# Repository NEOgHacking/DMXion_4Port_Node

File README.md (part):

# DMXion_4Port_Node
DMXion_4Port_Node is a DMX network node based on the official grandMA3 onPC 4Port Node 4k. My version also has 4DMX outputs with RDM support, a EtherCON connector for sturdy Ethernet connections and a display with a rotating knob for configuration. It also uses the Neutrik halo connectors with adressable rgb leds to show the status of the connection. But it also has some differences. First it unfortunately doesn't unlock any parameters in the GrandMA onPC software, but its 20x cheaper. About $100 instead of $2000.

# Features
This specific DMX node has some really usefull features.
1. 4DMX outputs with RDM support.
2. Neutrik EtherCON connector for a sturdy and lasting connection. Also support for ARTNET and sACN
3. Color display with a rotary encoder for configuration straigt from the unit itself.
4. UPS (uniteruptable power supply) For when the power cuts out but you still need it or just for battery operation.
5. Wifi card slot for wireless operation with the battery.
6. Powered by a rp2350 for its PIO modules so DMX is correctly implemented and not via a hacked uart or bitbanging a pin.
7. PoE (Power over Ethernet) For easy setup and as little wires as possible.
8. USB-C port for power and data to program the rp2350 or configure it.
9. Cheap PCB. The PCB is 100x72mm 4 layer so its cost is low only $7.

# Motivation
I started on making this DMX network node for a few reasons. First i was using a raspberry pi with a usb DMX dongle, this worked but was hard to set up and only got me 1 DMX universe without RDM. It also wasn't the cheapest setup. I wanted it to be cheaper and have more functionallity. Second I once had the opurtunity to use a grandMA3 onPC 4Port Node 4k at school once and realized how usefull it would be. Then my dumb brain said the same sentence it always says: "I can build that myself for cheaper right?" Next thing you know you are 100 hours deep into the project.

# Design
The design process was a heck of a ride, at first i started with the simple DMX part but then got to the ethernet. I really wanted PoE so started with the ride. It was a heck of a long ride, i think it took up 1/3 of the projects time its really complex. Also the most complex schematic from the whole project. The rest went pretty smooth. I had recently done another big project my 3D Printer mainboard and learned allot from that! So the rest was pretty straight forward, always some small chip changes here and there but apart from that it went well. The case design also went quick didn't have to high of standards for that but still wanted it to look good. After a whole day that was done. 
I used KiCad for PCB design, Onshape for 3D design and VScode for Firmware.

# Use
To use this product first get the firmware uploaded via the arduino IDE or PlatformIO Then just plug it into a ethernet setup and plug in your DMX devices. Thats it! Its that simple! For config use the display with the rotating knob to select universes, ethernet settings, ext.

# Schematic
This is a very long schematic. You can find the whole schematics in .PDF format in the individual PCB design folders. But here are some important ones.
First the main schematic of the main PCB.

Then the schematic of the display module.

And finally the esp wifi module.

# PCB's
So this project has 3 PCB's, first the main PCB that does all the hard work, then a display PCB with a rotary encoder and support components for a bare LCD and finally a custom made WIFI module PCB based on the esp.

(there is a glitch in this game, every project i do i get exactly 3 PCB's)

# Case
For this project there needed to be a case to protect the PCB from the outside world. I did this in onshape and am happy with the end result.

Here is the Onshape link:
https://cad.onshape.com/documents/7a1aa90c6a7c74ef8699231e/w/3ea57ea1703701009a206be9/e/21fe65d6bda3912845cd8de3?renderMode=0&uiState=69a73631645b04a633250657
<details>
  <summary>BOM</summary>
  
# BOM
| Id | Designator | Footprint | Quantity | Designation | Supplier and ref | Column1 | Needed quantity | - | LCSC | MOUSER | Already in another pcb | Enough? | Mrf# | Mfr. | Order Qty. | Unit Price(USD) | Ext.Price(USD) | LCSC#/MOUSER | Package | Min | Mult | SPQ | Availability | Stock Status | Customer Notes | Description | Matched status | Product Link |  |  |  |  |  |  |  |  |  |  |  |  |  |  |  |  |  |  |  |
| --- | --- | --- | --- | --- | --- | --- | --- | --- | --- | --- | --- | --- | --- | --- | --- | --- | --- | --- | --- | --- | --- | --- | --- | --- | --- | --- | --- | --- | --- | --- | --- | --- | --- | --- | --- | --- | --- | --- | --- | --- | --- | --- | --- | --- | --- | --- | --- |
| 17 | BT1 | JST_XH_B3B-XH-A_1x03_P2.50mm_Vertical | 1 | Battery_Cell |  |  | 2 |  | x |  |  |  | B3B-XH-A(LF)(SN) | JST | 10 | $0.05 | $0.50 | C144394 | Through Hole,P=2.5mm | 10 | 10 | 1000 | 61980 | In Stock |  | Connector Header 3 position 2.5mm Pitch 3A Through Hole -25?~+85? | Exact Matches | https://www.lcsc.com/product-detail/C144394.html |  |  |  |  |  |  |  |  |  |  |  |  |  |  |  |  |  |  |  |
| 6 | C12,C7,C5,C13,C11,C4,C6,C3,C9,C10,C8,C1 | C_0402_1005Metric | 12 | 100n |  |  | 24 |  | x |  |  |  | CL05B104KO5NNNC | Samsung Electro-Mechanics | 100 | $0.00 | $0.13 | C1525 | 402 | 100 | 100 | 10000 | 22016000 | In Stock |  | 100nF �10% 16V Ceramic Capacitor X7R 0402 | Exact Matches | https://www.lcsc.com/product-detail/C1525.html |  |  |  |  |  |  |  |  |  |  |  |  |  |  |  |  |  |  |  |
| 37 | C17,C19 | C_0402_1005Metric | 2 | 15p |  |  | 4 |  | x |  |  |  | CL05C150JB5NNNC | Samsung Electro-Mechanics | 100 | $0.00 | $0.37 | C86285 | 402 | 100 | 100 | 10000 | 454800 | In Stock |  | 15pF �5% 50V Ceramic Capacitor C0G 0402 | Exact Matches | https://www.lcsc.com/product-detail/C86285.html |  |  |  |  |  |  |  |  |  |  |  |  |  |  |  |  |  |  |  |
| 3 | C2,C15,C16,C14 | C_0402_1005Metric | 4 | 4u7 |  |  | 8 |  | x |  |  |  | CL05A475KP5NRNC | Samsung Electro-Mechanics | 50 | $0.01 | $0.31 | C368809 | 402 | 50 | 50 | 10000 | 5001000 | In Stock |  | 4.7uF �10% 10V Ceramic Capacitor X5R 0402 | Exact Matches | https://www.lcsc.com/product-detail/C368809.html |  |  |  |  |  |  |  |  |  |  |  |  |  |  |  |  |  |  |  |
| 9 | C20,C23,C57,C33,C21 | C_0603_1608Metric | 5 | 10n |  |  | 10 |  | x |  |  |  | CL10B103KC8NNNC | Samsung Electro-Mechanics | 100 | $0.01 | $0.62 | C84709 | 603 | 100 | 100 | 4000 | 18800 | In Stock |  | 10nF �10% 100V Ceramic Capacitor X7R 0603 | Exact Matches | https://www.lcsc.com/product-detail/C84709.html |  |  |  |  |  |  |  |  |  |  |  |  |  |  |  |  |  |  |  |
| 15 | C22,C36,C39,C41,C34,C38,C63,C37,C65,C47,C40,C35 | C_0603_1608Metric | 12 | 1n |  |  | 24 |  | x |  |  |  | CL10B102KC8NNNC | Samsung Electro-Mechanics | 50 | $0.01 | $0.25 | C153291 | 603 | 50 | 50 | 4000 | 107650 | In Stock |  | 1nF �10% 100V Ceramic Capacitor X7R 0603 | Exact Matches | https://www.lcsc.com/product-detail/C153291.html |  |  |  |  |  |  |  |  |  |  |  |  |  |  |  |  |  |  |  |
| 5 | C27,C76,C72,C70,C73,C64,C79,C60,C28,C74,C29,C88,C43,C78,C61,C71,C30,C66,C69,C68,C25,C42,C75,C67,C45,C31,C18,C26,C77 | C_0603_1608Metric | 29 | 100n |  |  | 58 |  | x |  |  |  | CL10B104KC8NNNC | Samsung Electro-Mechanics | 100 | $0.01 | $0.65 | C15725 | 603 | 50 | 50 | 4000 | 175750 | In Stock |  | 100nF �10% 100V Ceramic Capacitor X7R 0603 | Exact Matches | https://www.lcsc.com/product-detail/C15725.html |  |  |  |  |  |  |  |  |  |  |  |  |  |  |  |  |  |  |  |
| 63 | C32,C24 | CP_EIA-2012-12_Kemet-R | 2 | 10u |  |  | 4 |  | x |  |  |  | T491A106K006AT | KEMET | 5 | $0.18 | $0.91 | C122260 | CASE-A-3216-18(mm) | 5 | 5 | 2000 | 1980 | In Stock |  | 10uF �10% 6.3V Tantalum Capacitors 4?@100kHz CASE-A-3216-18(mm) | Exact Matches | https://www.lcsc.com/product-detail/C122260.html |  |  |  |  |  |  |  |  |  |  |  |  |  |  |  |  |  |  |  |
| 50 | C46,C44 | C_0603_1608Metric | 2 | 6.8n |  |  | 4 |  | x |  |  |  | CL10B682KB8NNNC | Samsung Electro-Mechanics | 100 | $0.01 | $0.68 | C84723 | 603 | 100 | 100 | 4000 | 5300 | In Stock |  | 6.8nF �10% 50V Ceramic Capacitor X7R 0603 | Exact Matches | https://www.lcsc.com/product-detail/C84723.html |  |  |  |  |  |  |  |  |  |  |  |  |  |  |  |  |  |  |  |
| 8 | C48,C49 | C_0603_1608Metric | 2 | 10p |  |  | 4 |  | x |  |  |  | CL10C100JB8NNNC | Samsung Electro-Mechanics | 100 | $0.01 | $0.50 | C1634 | 603 | 100 | 100 | 4000 | 1498600 | In Stock |  | 10pF �5% 50V Ceramic Capacitor C0G 0603 | Exact Matches | https://www.lcsc.com/product-detail/C1634.html |  |  |  |  |  |  |  |  |  |  |  |  |  |  |  |  |  |  |  |
| 41 | C52,C51,C50 | C_0805_2012Metric | 3 | 1u |  |  | 6 |  | x |  |  |  | C2012X7S2A105KT000N | TDK | 10 | $0.11 | $1.12 | C342785 | 805 | 5 | 5 | 2000 | 5645 | In Stock |  | 1uF �10% 100V Ceramic Capacitor X7S 0805 | Exact Matches | https://www.lcsc.com/product-detail/C342785.html |  |  |  |  |  |  |  |  |  |  |  |  |  |  |  |  |  |  |  |
| 57 | C53 | CP_Elec_6.3x5.8 | 1 | 10u |  |  | 2 |  | x |  |  |  | EEEFK1J100P | PANASONIC | 5 | $0.14 | $0.71 | C128459 | SMD,D6.3xL5.8mm | 5 | 5 | 1000 | 1420 | In Stock |  | 10uF �20% 63V Aluminum Electrolytic Capacitors 2000hrs@105? | Exact Matches | https://www.lcsc.com/product-detail/C128459.html |  |  |  |  |  |  |  |  |  |  |  |  |  |  |  |  |  |  |  |
| 69 | C54 | C_0603_1608Metric | 1 | 470p |  |  | 2 |  | x |  |  |  | CL10B471KB8NNNC | Samsung Electro-Mechanics | 100 | $0.01 | $0.56 | C22396 | 603 | 100 | 100 | 4000 | 189700 | In Stock |  | 470pF �10% 50V Ceramic Capacitor X7R 0603 | Exact Matches | https://www.lcsc.com/product-detail/C22396.html |  |  |  |  |  |  |  |  |  |  |  |  |  |  |  |  |  |  |  |
| 44 | C55 | CP_Elec_10x10.5 | 1 | 1000u |  |  | 2 |  | x |  |  |  | EEEFT1E102UP | PANASONIC | 2 | $0.78 | $1.55 | C401766 | SMD,D10xL10.2mm | 1 | 1 | 500 | 4041 | In Stock |  | 1000uF �20% 25V Aluminum Electrolytic Capacitors 2000hrs@105? | Exact Matches | https://www.lcsc.com/product-detail/C401766.html |  |  |  |  |  |  |  |  |  |  |  |  |  |  |  |  |  |  |  |
| 52 | C56 | C_1206_3216Metric | 1 | 100u |  |  | 2 |  | x |  |  |  | CL31A107MQHNNNE | Samsung Electro-Mechanics | 10 | $0.06 | $0.61 | C15008 | 1206 | 10 | 10 | 2000 | 6009890 | In Stock |  | 100uF �20% 6.3V Ceramic Capacitor X5R 1206 | Exact Matches | https://www.lcsc.com/product-detail/C15008.html |  |  |  |  |  |  |  |  |  |  |  |  |  |  |  |  |  |  |  |
| 14 | C58 | C_0603_1608Metric | 1 | 4u7 |  |  | 2 |  | x |  |  |  | CL10A475KP8NNNC | Samsung Electro-Mechanics | 50 | $0.01 | $0.28 | C1705 | 603 | 50 | 50 | 4000 | 13333100 | In Stock |  | 4.7uF �10% 10V Ceramic Capacitor X5R 0603 | Exact Matches | https://www.lcsc.com/product-detail/C1705.html |  |  |  |  |  |  |  |  |  |  |  |  |  |  |  |  |  |  |  |
| 20 | C59 | C_0603_1608Metric | 1 | 3.3n |  |  | 2 |  | x |  |  |  | CL10B332KB8NNNC | Samsung Electro-Mechanics | 20 | $0.01 | $0.11 | C1613 | 603 | 20 | 20 | 4000 | 61420 | In Stock |  | 3.3nF �10% 50V Ceramic Capacitor X7R 0603 | Exact Matches | https://www.lcsc.com/product-detail/C1613.html |  |  |  |  |  |  |  |  |  |  |  |  |  |  |  |  |  |  |  |
| 42 | C62 | C_0603_1608Metric | 1 | 15n |  |  | 2 |  | x |  |  |  | CL10B153KB8NNNC | Samsung Electro-Mechanics | 20 | $0.01 | $0.16 | C296713 | 603 | 20 | 20 | 4000 | 39800 | In Stock |  | 15nF �10% 50V Ceramic Capacitor X7R 0603 | Exact Matches | https://www.lcsc.com/product-detail/C296713.html |  |  |  |  |  |  |  |  |  |  |  |  |  |  |  |  |  |  |  |
| 10 | C80,C81 | C_0603_1608Metric | 2 | 1u |  |  | 4 |  | x |  |  |  | CL10A105KB8NNNC | Samsung Electro-Mechanics | 50 | $0.01 | $0.28 | C15849 | 603 | 50 | 50 | 4000 | 4548950 | In Stock |  | 1uF �10% 50V Ceramic Capacitor X5R 0603 | Exact Matches | https://www.lcsc.com/product-detail/C15849.html |  |  |  |  |  |  |  |  |  |  |  |  |  |  |  |  |  |  |  |
| 53 | C82,C86,C87,C83,C84 | C_0603_1608Metric | 5 | 10u |  |  | 10 |  | x |  |  |  | CL10A106KP8NNNC | Samsung Electro-Mechanics | 50 | $0.01 | $0.33 | C19702 | 603 | 50 | 50 | 4000 | 13475400 | In Stock |  | 10uF �10% 10V Ceramic Capacitor X5R 0603 | Exact Matches | https://www.lcsc.com/product-detail/C19702.html |  |  |  |  |  |  |  |  |  |  |  |  |  |  |  |  |  |  |  |
| 58 | C85 | C_0603_1608Metric | 1 | 2u2 |  |  | 2 |  | x |  |  |  | CL10A225KO8NNNC | Samsung Electro-Mechanics | 50 | $0.01 | $0.31 | C23630 | 603 | 50 | 50 | 4000 | 5941500 | In Stock |  | 2.2uF �10% 16V Ceramic Capacitor X5R 0603 | Exact Matches | https://www.lcsc.com/product-detail/C23630.html |  |  |  |  |  |  |  |  |  |  |  |  |  |  |  |  |  |  |  |
| 32 | D1 | D_SOD-123F | 1 | DSK24L |  |  | 2 |  | x |  |  |  | DSK24L | LGE | 10 | $0.06 | $0.62 | C19272974 | SOD-123FL | 10 | 10 | 3000 | 2600 | In Stock |  | Diode Independent 40V 2A Surface Mount SOD-123FL | Exact Matches | https://www.lcsc.com/product-detail/C19272974.html |  |  |  |  |  |  |  |  |  |  |  |  |  |  |  |  |  |  |  |
| 56 | D10 | D_SMA | 1 | SS34 |  |  | 2 |  | x |  |  |  | SS34 | GOODWORK | 20 | $0.03 | $0.56 | C908680 | SMA(DO-214AC) | 20 | 20 | 5000 | 202260 | In Stock |  | Diode Independent 40V 3A Surface Mount SMA(DO-214AC) | Exact Matches | https://www.lcsc.com/product-detail/C908680.html |  |  |  |  |  |  |  |  |  |  |  |  |  |  |  |  |  |  |  |
| 49 | D11 | D_SOD-123 | 1 | 1N4148W |  |  | 2 |  | x |  |  |  | 1N4148W-E3-08 | VISHAY | 5 | $0.03 | $0.17 | C241939 | SOD-123 | 5 | 5 | 3000 | 71145 | In Stock |  | Diode Independent 75V 150mA Surface Mount SOD-123 | Exact Matches | https://www.lcsc.com/product-detail/C241939.html |  |  |  |  |  |  |  |  |  |  |  |  |  |  |  |  |  |  |  |
| 66 | D12 | D_SOD-123F | 1 | DFTL30A |  |  | 2 |  | x |  |  |  | P4FL30A_R1_00001 | PANJIT | 5 | $0.09 | $0.43 | C2902532 | SOD-123FL | 5 | 5 | 3000 | 2220 | In Stock |  | 48.4VC Clamp 8.3A@10/1000us Ipp TVS DIODE SOD-123FL | Exact Matches | https://www.lcsc.com/product-detail/C2902532.html |  |  |  |  |  |  |  |  |  |  |  |  |  |  |  |  |  |  |  |
| 11 | D13 | LED-SMD_4P-L1.6-W1.5-TR | 1 | LED_ABGR |  |  | 2 |  | x |  |  |  | DY-S161506BRGC-T5-4T-03 | TONYU | 10 | $0.04 | $0.37 | C7280953 | SMD,1.6x1.5mm | 10 | 10 | 4000 | 1640 | In Stock |  | Red, Green, Blue 630nm LED Indication - Discrete 1.8V~2.4V SMD,1.5x1.6mm | Exact Matches | https://www.lcsc.com/product-detail/C7280953.html |  |  |  |  |  |  |  |  |  |  |  |  |  |  |  |  |  |  |  |
| 28 | D2,D7,D5,D6,D9,D3,D4,D8 | D_SOD-123F | 8 | SL110PL-TP |  |  | 16 |  | x |  |  |  | SL110PL-TP | MCC | 20 | $0.15 | $3.07 | C7080765 | SOD-123FL | 10 | 10 | 2500 | 4140 | In Stock |  | Diode 100V 1A Surface Mount SOD-123FL | Exact Matches | https://www.lcsc.com/product-detail/C7080765.html |  |  |  |  |  |  |  |  |  |  |  |  |  |  |  |  |  |  |  |
| 62 | IC1 | QFN-32-1EP_5x5mm_P0.5mm_EP3.45x3.45mm_ThermalVias | 1 | NPM1300-QEAA-R7 |  |  | 2 |  |  | x |  |  | nPM1300-QEAA-R7 | Nordic Semiconductor | 2 | $1.54 | $3.08 | 949-NPM1300-QEAA-R7 |  |  |  |  |  |  |  |  |  | https://nl.mouser.com/ProductDetail/Nordic-Semiconductor/nPM1300-QEAA-R7?qs=3pZoU%2F6IRTj0hxAp51B2zA%3D%3D |  |  |  |  |  |  |  |  |  |  |  |  |  |  |  |  |  |  |  |
| 33 | J1 | JST_SH_SM03B-SRSS-TB_1x03-1MP_P1.00mm_Horizontal | 1 | Conn_01x03_MountingPin |  |  | 2 |  | x |  |  |  | SM03B-SRSS-TB(LF)(SN) | JST | 5 | $0.17 | $0.87 | C160403 | SMD,P=1mm,Surface Mount,Right Angle | 5 | 5 | 3000 | 47315 | In Stock |  | Connector Header 3 position 1mm Pitch 1A Surface Mount, Right Angle -25?~+85? | Exact Matches | https://www.lcsc.com/product-detail/C160403.html |  |  |  |  |  |  |  |  |  |  |  |  |  |  |  |  |  |  |  |
| 39 | J12 | IDC-Header_2x06_P2.54mm_Vertical | 1 | IDC |  |  | 2 |  | x |  |  |  | 2.54-2*6P | BOOMELE(Boom Precision Elec) | 5 | $0.11 | $0.57 | C9136 | Through Hole,P=2.54mm | 5 | 5 | 220 | 19840 | In Stock |  | Connector IDC Header Through Hole 12 position 2.54mm | Exact Matches | https://www.lcsc.com/product-detail/C9136.html |  |  |  |  |  |  |  |  |  |  |  |  |  |  |  |  |  |  |  |
| 51 | J13 | PinSocket_2x04_P2.54mm_Vertical | 1 | Conn_02x04 |  |  | 2 |  | x |  |  |  | PM254V-12-08-H85 | XFCN | 5 | $0.11 | $0.56 | C2834799 | Through Hole,P=2.54mm | 5 | 5 | 1000 | 26375 | In Stock |  | Female Header 8 Position 2.54mm Pitch Dual Row Through Hole -40?~+105? | Exact Matches | https://www.lcsc.com/product-detail/C2834799.html |  |  |  |  |  |  |  |  |  |  |  |  |  |  |  |  |  |  |  |
| 13 | J2 | USB-C_SMD-TYPE-C-31-M-12_1 | 1 | USB_C_Receptacle_USB2.0_14P |  |  | 2 |  | x |  |  |  | TYPE-C-31-M-12 | Korean Hroparts Elec | 5 | $0.17 | $0.84 | C165948 | SMD | 5 | 5 | 1000 | 263130 | In Stock |  | USB-C (USB TYPE-C) Receptacle Connector 16 Position Surface Mount | Exact Matches | https://www.lcsc.com/product-detail/C165948.html |  |  |  |  |  |  |  |  |  |  |  |  |  |  |  |  |  |  |  |
| 1 | J3 | NE8FAHLRDAE | 1 | RJ45 |  |  | 2 |  |  | x |  |  | NE8FAH-LR-DAE | Neutrik | 2 | $6.73 | $13.46 | 568-NE8FAH-LR-DAE |  |  |  |  |  |  |  |  |  | https://nl.mouser.com/ProductDetail/Neutrik/NE8FAH-LR-DAE?qs=4ASt3YYao0WhX9cY4j%252BFSA%3D%3D |  |  |  |  |  |  |  |  |  |  |  |  |  |  |  |  |  |  |  |
| 12 | J4,J8,J10,J6 | NC5FAH1-LR-DAE | 4 | XLR5 |  |  | 4 |  |  | x |  |  | NC5FAH1-LR-DAE | Neutrik | 4 | $7.79 | $31.16 | 568-NC5FAH1-LR-DAE |  |  |  |  |  |  |  |  |  | https://nl.mouser.com/ProductDetail/Neutrik/NC5FAH1-LR-DAE?qs=6avfeC6zeS5u3oz5Q9UQlw%3D%3D |  |  |  |  |  |  |  |  |  |  |  |  |  |  |  |  |  |  |  |
| 47 | J7,J11,J5,J9 | NC3FAH2-LR-DAE | 4 | XLR3 |  |  | 4 |  |  | x |  |  | NC3FAH2-LR-DAE | Neutrik | 4 | $4.33 | $17.32 | 568-NC3FAH2-LR-DAE |  |  |  |  |  |  |  |  |  | https://nl.mouser.com/ProductDetail/Neutrik/NC3FAH2-LR-DAE?qs=4ASt3YYao0XSl5KoEkZrIA%3D%3D |  |  |  |  |  |  |  |  |  |  |  |  |  |  |  |  |  |  |  |
| 21 | L1 | IND-SMD_L2.0-W1.6_AOTA-B201610S3R3-101-T | 1 | 3.3u |  |  | 2 |  | x |  |  |  | AOTA-B201610S3R3-101-T | ABRACON | 5 | $0.29 | $1.44 | C42411119 | 806 | 5 | 5 | 3000 | 15360 | In Stock |  | 2.1A 3.3uH 115m? 2.4A Molded Inductor 0806 Fixed Inductors RoHS | Exact Matches | https://www.lcsc.com/product-detail/C42411119.html |  |  |  |  |  |  |  |  |  |  |  |  |  |  |  |  |  |  |  |
| 48 | L2 | L_Vishay_IHLP-1616 | 1 | 1u |  |  | 2 |  | x |  |  |  | IHLP1616BZER1R0M11 | VISHAY | 2 | $1.63 | $3.26 | C844978 | 1616 | 1 | 1 | 4000 | 79 | In Stock |  | 4.5A 1uH 27m? 5A �20% 1616 Fixed Inductors RoHS | Exact Matches | https://www.lcsc.com/product-detail/C844978.html |  |  |  |  |  |  |  |  |  |  |  |  |  |  |  |  |  |  |  |
| 22 | L3 | XFMR-SMD_16P-L12.7-W7.1-P1.27-LS9.4-BL | 1 | H2019NLT |  |  | 2 |  | x |  |  |  | H2019NLT | PULSE | 2 | $0.74 | $1.49 | C110250 | SMD,12.7x7.1mm | 1 | 1 | 600 | 2085 | In Stock |  | LAN Transformer 1CT:1CT Surface Mount,12.7x7.1mm | Exact Matches | https://www.lcsc.com/product-detail/C110250.html |  |  |  |  |  |  |  |  |  |  |  |  |  |  |  |  |  |  |  |
| 30 | L4,L5 | L_0805_2012Metric | 2 | 2u2 |  |  | 4 |  | x |  |  |  | MLP2012H2R2MT0S1 | TDK | 10 | $0.08 | $0.84 | C383369 | 805 | 10 | 10 | 4000 | 89820 | In Stock |  | 1A 2.2uH 195m? �20% 0805 Fixed Inductors RoHS | Exact Matches | https://www.lcsc.com/product-detail/C383369.html |  |  |  |  |  |  |  |  |  |  |  |  |  |  |  |  |  |  |  |
| 16 | LED1,LED5,LED6,LED3,LED8,LED10,LED9,LED2,LED4,LED7 | LED-SMD_4P-L1.5-W1.5-BL | 10 | SK6805-EC15 |  |  | 20 |  | x |  |  |  | SK6805-EC15 | OPSCO Optoelectronics | 45 | $0.09 | $4.04 | C2890035 | SMD-4P,1.5x1.5mm | 5 | 5 | 4500 | 259070 | In Stock |  | SMD-4P,1.5x1.5mm LED Addressable, Specialty RoHS | Exact Matches | https://www.lcsc.com/product-detail/C2890035.html |  |  |  |  |  |  |  |  |  |  |  |  |  |  |  |  |  |  |  |
| 29 | R1,R27,R3 | R_0603_1608Metric | 3 | 1k |  |  | 6 |  | x |  |  |  | RC0603FR-071KL | YAGEO | 100 | $0.00 | $0.14 | C22548 | 603 | 100 | 100 | 5000 | 4596000 | In Stock |  | 100mW 1k? 75V Thick Film Resistor �100ppm/? �1% 0603 Chip Resistor - Surface Mount RoHS | Exact Matches | https://www.lcsc.com/product-detail/C22548.html |  |  |  |  |  |  |  |  |  |  |  |  |  |  |  |  |  |  |  |
| 34 | R11,R43,R7,R42 | R_0603_1608Metric | 4 | 10k |  |  | 8 |  | x |  |  |  | RC0603FR-0710KL | YAGEO | 100 | $0.00 | $0.14 | C98220 | 603 | 100 | 100 | 5000 | 9034300 | In Stock |  | 100mW 10k? 75V Thick Film Resistor �100ppm/? �1% 0603 Chip Resistor - Surface Mount RoHS | Exact Matches | https://www.lcsc.com/product-detail/C98220.html |  |  |  |  |  |  |  |  |  |  |  |  |  |  |  |  |  |  |  |
| 19 | R13,R12,R15,R14 | R_0603_1608Metric | 4 | 33R |  |  | 8 |  | x |  |  |  | RC0603FR-0733RL | YAGEO | 100 | $0.00 | $0.15 | C108661 | 603 | 100 | 100 | 5000 | 1912100 | In Stock |  | 100mW 33? 75V Thick Film Resistor �100ppm/? �1% 0603 Chip Resistor - Surface Mount RoHS | Exact Matches | https://www.lcsc.com/product-detail/C108661.html |  |  |  |  |  |  |  |  |  |  |  |  |  |  |  |  |  |  |  |
| 38 | R16 | R_0603_1608Metric | 1 | 1M |  |  | 2 |  | x |  |  |  | RC0603FR-071ML | YAGEO | 100 | $0.00 | $0.15 | C105578 | 603 | 100 | 100 | 5000 | 711300 | In Stock |  | 100mW 1M? 75V Thick Film Resistor �100ppm/? �1% 0603 Chip Resistor - Surface Mount RoHS | Exact Matches | https://www.lcsc.com/product-detail/C105578.html |  |  |  |  |  |  |  |  |  |  |  |  |  |  |  |  |  |  |  |
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
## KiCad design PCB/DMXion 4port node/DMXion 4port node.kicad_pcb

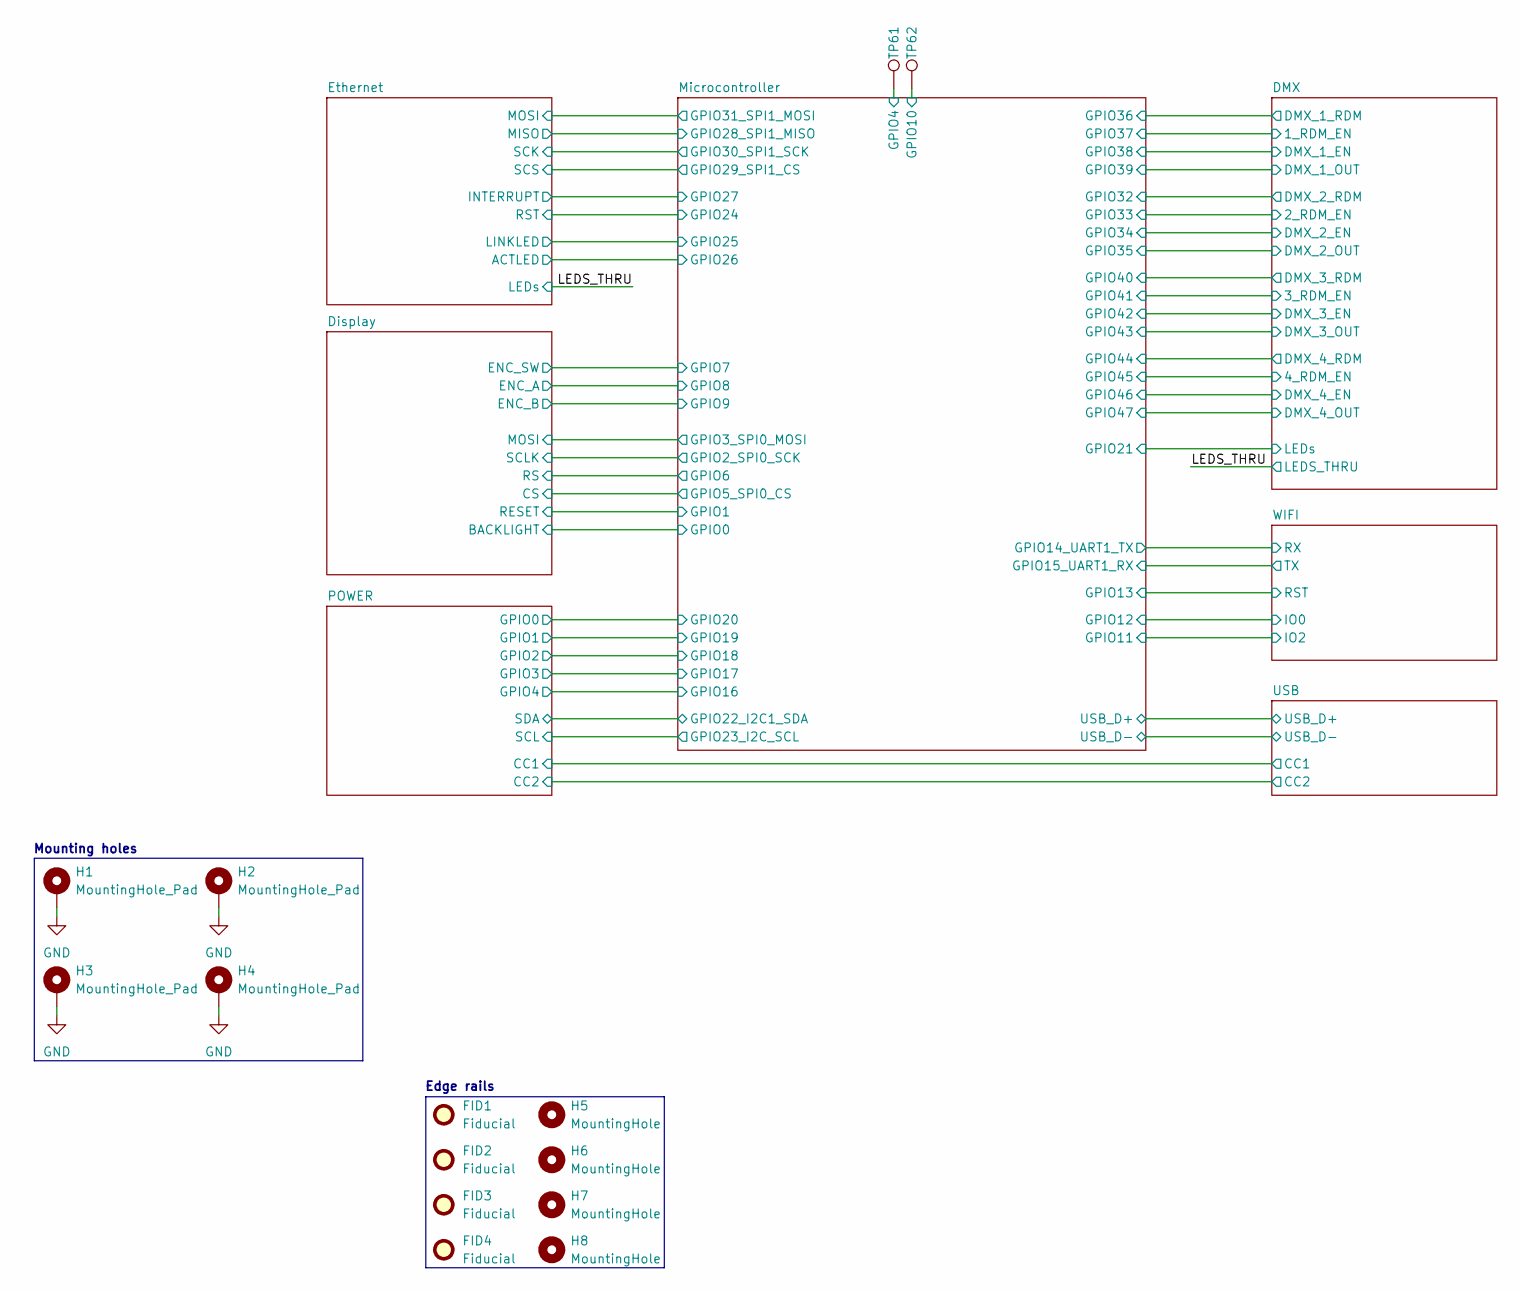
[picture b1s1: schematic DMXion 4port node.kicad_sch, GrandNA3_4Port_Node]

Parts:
FID1, FID2, FID3, FID4: Fiducial; Fiducial_1mm_Mask2mm
H1, H2, H3, H4: MountingHole_Pad; MountingHole_3.2mm_M3_Pad
H5, H6, H7, H8: MountingHole; MountingHole_2mm
TP61, TP62: TestPoint; TestPoint_Pad_D1.5mm

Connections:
/Microcontroller/GPIO4: TP61.1 (1_1); also elsewhere on the board
/Microcontroller/GPIO10: TP62.1 (1_1); also elsewhere on the board
GND: H1.1 (1_1), H2.1 (1_1), H3.1 (1_1), H4.1 (1_1); also elsewhere on the board

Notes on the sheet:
Edge rails
Mounting holes

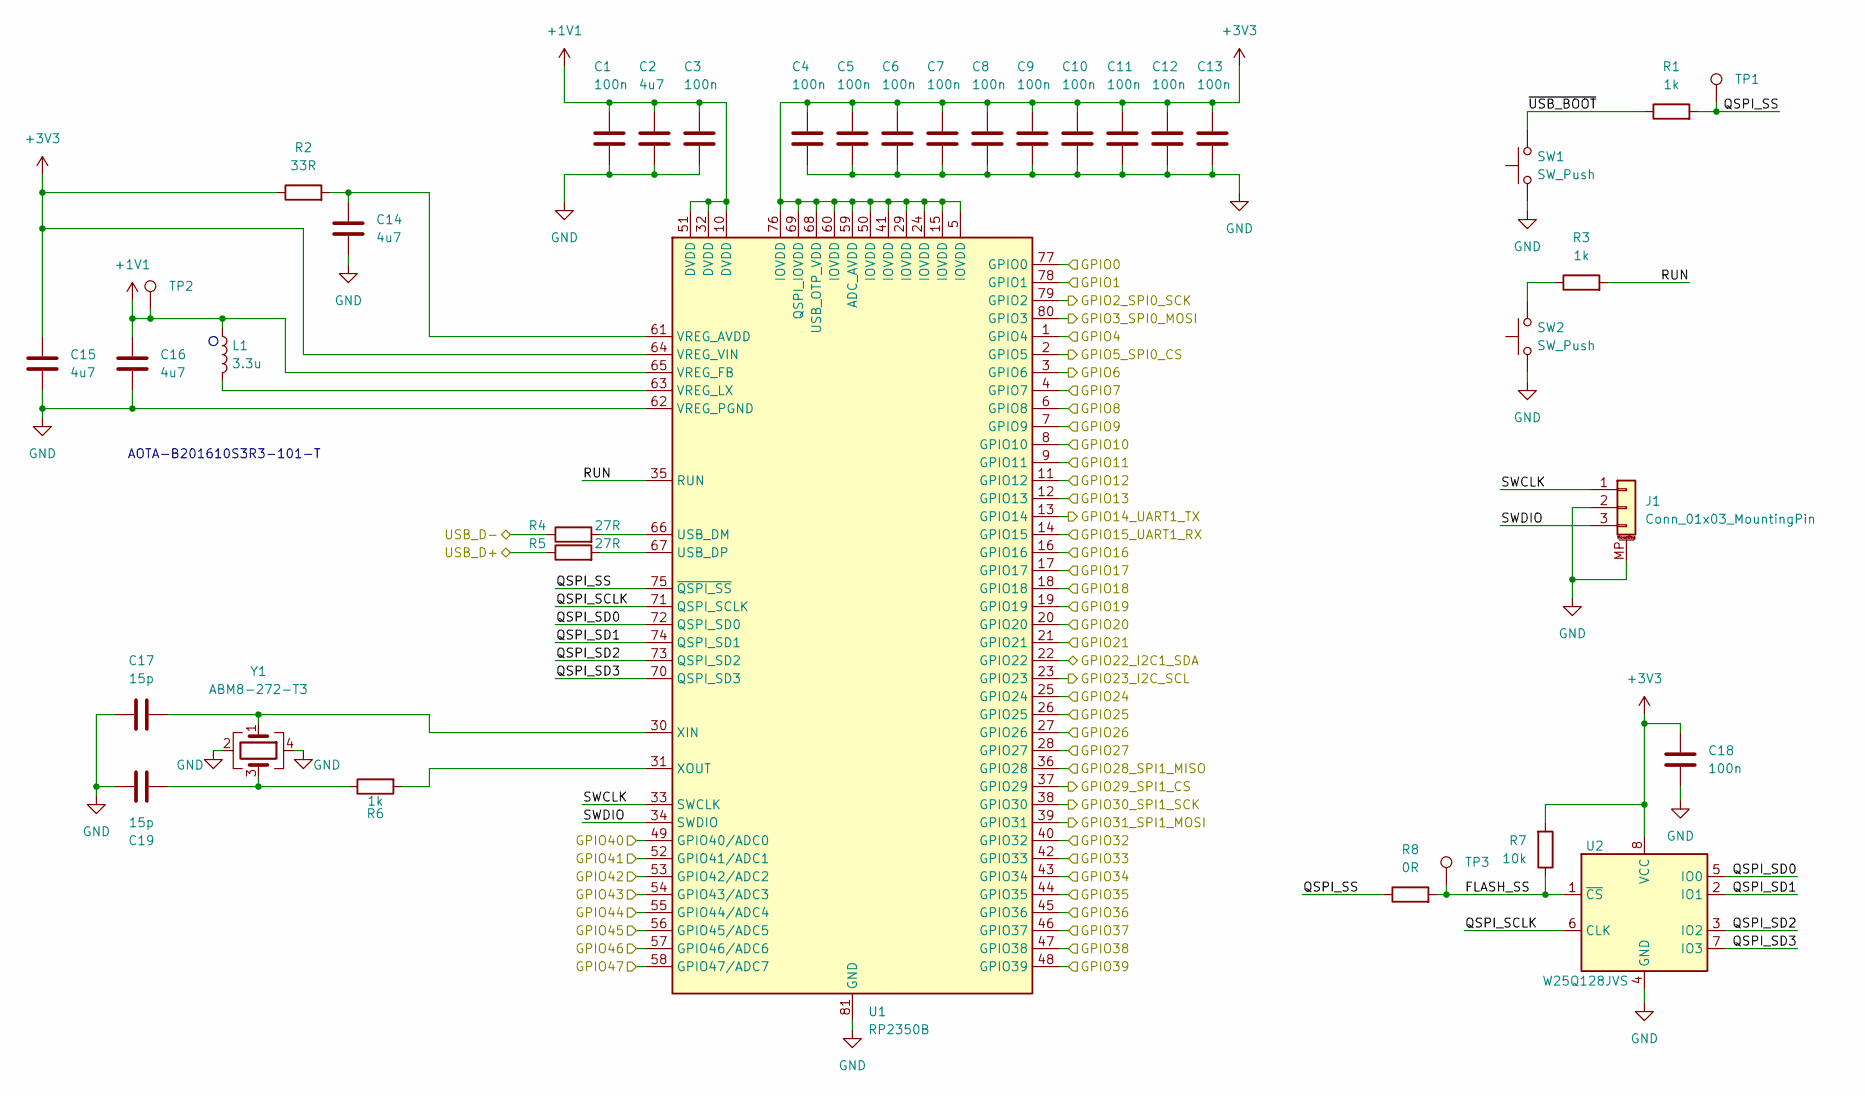
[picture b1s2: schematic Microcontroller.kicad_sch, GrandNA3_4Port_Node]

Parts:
C1, C3, C4, C5, C6, C7, C8, C9, C10, C11, C12, C13: 100n; C_0402_1005Metric
C2, C14: 4u7; C_0402_1005Metric
C15, C16: 4u7; C_0402_1005Metric_small_pads
C17, C19: 15p; C_0402_1005Metric
C18: 100n; C_0603_1608Metric
J1: Conn_01x03_MountingPin; JST_SH_SM03B-SRSS-TB_1x03-1MP_P1.00mm_Horizontal
L1: 3.3u; L_pol_2016
R1, R3: 1k; R_0603_1608Metric
R2: 33R; R_0402_1005Metric
R4, R5: 27R; R_0402_1005Metric
R6: 1k; R_0402_1005Metric
R7: 10k; R_0603_1608Metric
R8: 0R; R_0603_1608Metric
SW1, SW2: SW_Push; SW_SPST_B3U-1000P
TP1, TP2, TP3: TestPoint; TestPoint_Pad_D1.5mm
U1: RP2350B; RP2350-QFN-80-1EP_10x10_P0.4mm_EP3.4x3.4mm_ThermalVias
U2: W25Q128JVS; SOIC-8_5.3x5.3mm_P1.27mm
Y1: ABM8-272-T3; Crystal_SMD_3225-4Pin_3.2x2.5mm

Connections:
+1V1: C1.1, C2.1, C3.1, C16.1, L1.1, TP2.1 (1_1), U1.10 (DVDD), U1.32 (DVDD), U1.51 (DVDD), U1.65 (VREG_FB)
+3V3: C4.1, C5.1, C6.1, C7.1, C8.1, C9.1, C10.1, C11.1, C12.1, C13.1, C15.1, C18.1, R2.1, R7.2, U1.5 (IOVDD), U1.15 (IOVDD), U1.24 (IOVDD), U1.29 (IOVDD), U1.41 (IOVDD), U1.50 (IOVDD), U1.59 (ADC_AVDD), U1.60 (IOVDD), U1.64 (VREG_VIN), U1.68 (USB_OTP_VDD), U1.69 (QSPI_IOVDD), U1.76 (IOVDD), U2.8 (VCC); also elsewhere on the board
/DMX/1_RDM_EN: U1.46 (GPIO37); also elsewhere on the board
/DMX/2_RDM_EN: U1.42 (GPIO33); also elsewhere on the board
/DMX/3_RDM_EN: U1.52 (GPIO41/ADC1); also elsewhere on the board
/DMX/4_RDM_EN: U1.56 (GPIO45/ADC5); also elsewhere on the board
/DMX/DMX_1_EN: U1.47 (GPIO38); also elsewhere on the board
/DMX/DMX_1_OUT: U1.48 (GPIO39); also elsewhere on the board
/DMX/DMX_1_RDM: U1.45 (GPIO36); also elsewhere on the board
/DMX/DMX_2_EN: U1.43 (GPIO34); also elsewhere on the board
/DMX/DMX_2_OUT: U1.44 (GPIO35); also elsewhere on the board
/DMX/DMX_2_RDM: U1.40 (GPIO32); also elsewhere on the board
/DMX/DMX_3_EN: U1.53 (GPIO42/ADC2); also elsewhere on the board
/DMX/DMX_3_OUT: U1.54 (GPIO43/ADC3); also elsewhere on the board
/DMX/DMX_3_RDM: U1.49 (GPIO40/ADC0); also elsewhere on the board
/DMX/DMX_4_EN: U1.57 (GPIO46/ADC6); also elsewhere on the board
/DMX/DMX_4_OUT: U1.58 (GPIO47/ADC7); also elsewhere on the board
/DMX/DMX_4_RDM: U1.55 (GPIO44/ADC4); also elsewhere on the board
/DMX/LEDs: U1.21 (GPIO21); also elsewhere on the board
/Display/BACKLIGHT: U1.77 (GPIO0); also elsewhere on the board
/Display/CS: U1.2 (GPIO5); also elsewhere on the board
/Display/ENC_A: U1.6 (GPIO8); also elsewhere on the board
/Display/ENC_B: U1.7 (GPIO9); also elsewhere on the board
/Display/ENC_SW: U1.4 (GPIO7); also elsewhere on the board
/Display/MOSI: U1.80 (GPIO3); also elsewhere on the board
/Display/RESET: U1.78 (GPIO1); also elsewhere on the board
/Display/RS: U1.3 (GPIO6); also elsewhere on the board
/Display/SCLK: U1.79 (GPIO2); also elsewhere on the board
/Ethernet/ACTLED: U1.27 (GPIO26); also elsewhere on the board
/Ethernet/INTERRUPT: U1.28 (GPIO27); also elsewhere on the board
/Ethernet/LINKLED: U1.26 (GPIO25); also elsewhere on the board
/Ethernet/MISO: U1.36 (GPIO28); also elsewhere on the board
/Ethernet/MOSI: U1.39 (GPIO31); also elsewhere on the board
/Ethernet/RST: U1.25 (GPIO24); also elsewhere on the board
/Ethernet/SCK: U1.38 (GPIO30); also elsewhere on the board
/Ethernet/SCS: U1.37 (GPIO29); also elsewhere on the board
/Microcontroller/FLASH_SS: R7.1, R8.2, TP3.1 (1_1), U2.1 (~CS)
/Microcontroller/GPIO4: U1.1 (GPIO4); also elsewhere on the board
/Microcontroller/GPIO10: U1.8 (GPIO10); also elsewhere on the board
/Microcontroller/GPIO11: U1.9 (GPIO11); also elsewhere on the board
/Microcontroller/GPIO12: U1.11 (GPIO12); also elsewhere on the board
/Microcontroller/GPIO13: U1.12 (GPIO13); also elsewhere on the board
/Microcontroller/GPIO14_UART1_TX: U1.13 (GPIO14); also elsewhere on the board
/Microcontroller/GPIO15_UART1_RX: U1.14 (GPIO15); also elsewhere on the board
/Microcontroller/GPIO16: U1.16 (GPIO16); also elsewhere on the board
/Microcontroller/GPIO17: U1.17 (GPIO17); also elsewhere on the board
/Microcontroller/GPIO18: U1.18 (GPIO18); also elsewhere on the board
/Microcontroller/GPIO19: U1.19 (GPIO19); also elsewhere on the board
/Microcontroller/GPIO20: U1.20 (GPIO20); also elsewhere on the board
/Microcontroller/GPIO22_I2C1_SDA: U1.22 (GPIO22); also elsewhere on the board
/Microcontroller/GPIO23_I2C_SCL: U1.23 (GPIO23); also elsewhere on the board
/Microcontroller/QSPI_SCLK: U1.71 (QSPI_SCLK), U2.6 (CLK)
/Microcontroller/QSPI_SD0: U1.72 (QSPI_SD0), U2.5 (IO0)
/Microcontroller/QSPI_SD1: U1.74 (QSPI_SD1), U2.2 (IO1)
/Microcontroller/QSPI_SD2: U1.73 (QSPI_SD2), U2.3 (IO2)
/Microcontroller/QSPI_SD3: U1.70 (QSPI_SD3), U2.7 (IO3)
/Microcontroller/QSPI_SS: R1.2, R8.1, TP1.1 (1_1), U1.75 (~QSPI_SS)
/Microcontroller/RUN: R3.2, U1.35 (RUN)
/Microcontroller/SWCLK: J1.1, U1.33 (SWCLK)
/Microcontroller/SWDIO: J1.3, U1.34 (SWDIO)
/Microcontroller/~USB_BOOT: R1.1, SW1.2
/USB/USB_D+: R5.1; also elsewhere on the board
/USB/USB_D-: R4.1; also elsewhere on the board
GND: C1.2, C2.2, C3.2, C4.2, C5.2, C6.2, C7.2, C8.2, C9.2, C10.2, C11.2, C12.2, C13.2, C14.2, C15.2, C16.2, C17.1, C18.2, C19.1, J1.2, J1.MP (MountPin), SW1.1, SW2.1, U1.62 (VREG_PGND), U1.81 (GND), U2.4 (GND), Y1.2 (G), Y1.4 (G); also elsewhere on the board
unnamed: C19.2, R6.1, Y1.3
unnamed: R3.1, SW2.2
unnamed: R4.2, U1.66 (USB_DM)
unnamed: R5.2, U1.67 (USB_DP)
unnamed: C14.1, R2.2, U1.61 (VREG_AVDD)
unnamed: L1.2, U1.63 (VREG_LX)
unnamed: C17.2, U1.30 (XIN), Y1.1
unnamed: R6.2, U1.31 (XOUT)

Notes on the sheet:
AOTA-B201610S3R3-101-T

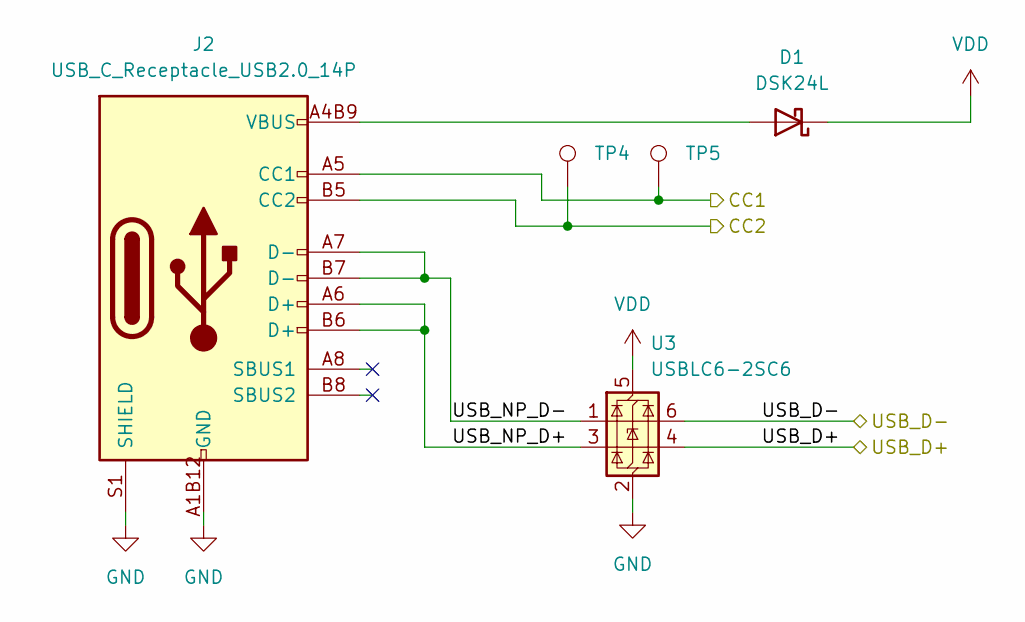
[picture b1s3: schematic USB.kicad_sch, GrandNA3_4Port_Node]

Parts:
D1: DSK24L; D_SOD-123F
J2: USB_C_Receptacle_USB2.0_14P; USB-C_SMD-TYPE-C-31-M-12_1
TP4, TP5: TestPoint; TestPoint_Pad_D1.5mm
U3: USBLC6-2SC6; SOT-23-6

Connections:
/POWER/CC1: J2.A5 (CC1), TP5.1 (1_1); also elsewhere on the board
/POWER/CC2: J2.B5 (CC2), TP4.1 (1_1); also elsewhere on the board
/USB/USB_D+: U3.4 (I/O2); also elsewhere on the board
/USB/USB_D-: U3.6 (I/O1); also elsewhere on the board
/USB/USB_NP_D+: J2.A6 (D+), J2.B6 (D+), U3.3 (I/O2)
/USB/USB_NP_D-: J2.A7 (D-), J2.B7 (D-), U3.1 (I/O1)
GND: J2.A1B12 (GND), J2.B1A12 (GND), J2.S1 (SHIELD), U3.2 (GND); also elsewhere on the board
unnamed: D1.2 (A), J2.A4B9 (VBUS), J2.B4A9 (VBUS)
VDD: D1.1 (K), U3.5 (VBUS); also elsewhere on the board

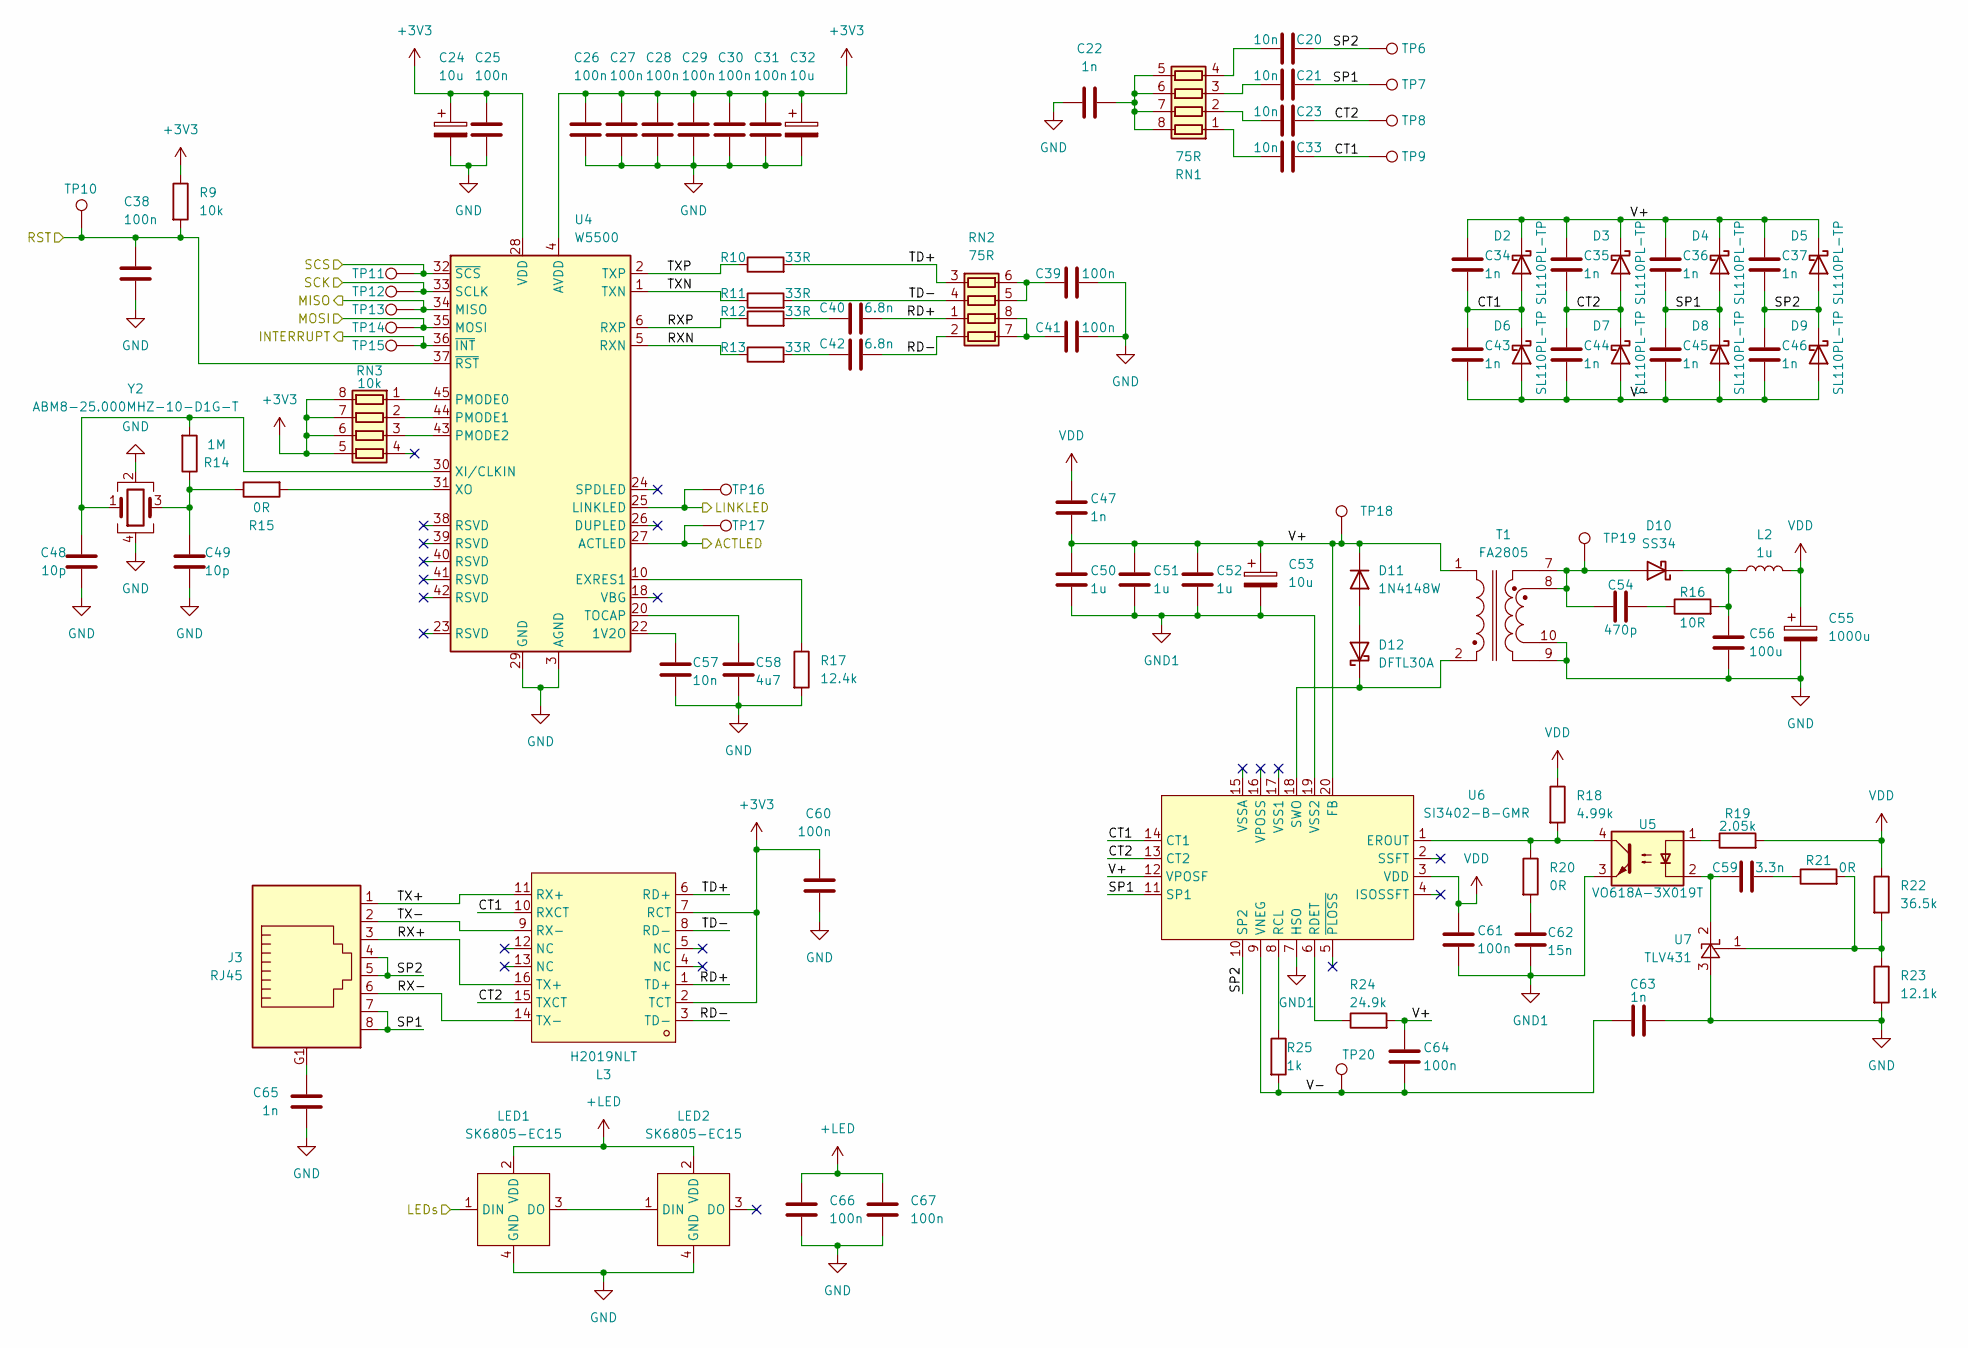
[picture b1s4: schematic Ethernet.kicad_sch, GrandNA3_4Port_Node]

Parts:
C20, C21, C23, C33, C57: 10n; C_0603_1608Metric
C22, C34, C35, C36, C37, C43, C44, C45, C46, C47, C63, C65: 1n; C_0603_1608Metric
C24, C32: 10u; CP_EIA-2012-12_Kemet-R
C25, C26, C27, C28, C29, C30, C31, C38, C39, C41, C60, C61, C64, C66, C67: 100n; C_0603_1608Metric
C40, C42: 6.8n; C_0603_1608Metric
C48, C49: 10p; C_0603_1608Metric
C50, C51, C52: 1u; C_0805_2012Metric
C53: 10u; CP_Elec_6.3x5.8
C54: 470p; C_0603_1608Metric
C55: 1000u; CP_Elec_10x10.5
C56: 100u; C_1206_3216Metric
C58: 4u7; C_0603_1608Metric
C59: 3.3n; C_0603_1608Metric
C62: 15n; C_0603_1608Metric
D2, D3, D4, D5, D6, D7, D8, D9: SL110PL-TP; D_SOD-123F
D10: SS34; D_SMA
D11: 1N4148W; D_SOD-123
D12: DFTL30A; D_SOD-123F
J3: RJ45; NE8FAHLRDAE
L2: 1u; L_Vishay_IHLP-1616
L3: H2019NLT; XFMR-SMD_16P-L12.7-W7.1-P1.27-LS9.4-BL; LCSC Part C110250
LED1, LED2: SK6805-EC15; LED-SMD_4P-L1.5-W1.5-BL; LCSC Part C2890035
R9: 10k; R_0603_1608Metric
R10, R11, R12, R13: 33R; R_0603_1608Metric
R14: 1M; R_0603_1608Metric
R15, R20, R21: 0R; R_0603_1608Metric
R16: 10R; R_0603_1608Metric
R17: 12.4k; R_0603_1608Metric
R18: 4.99k; R_0603_1608Metric
R19: 2.05k; R_0603_1608Metric
R22: 36.5k; R_0603_1608Metric
R23: 12.1k; R_0603_1608Metric
R24: 24.9k; R_0603_1608Metric
R25: 1k; R_0603_1608Metric
RN1, RN2: 75R; R_Array_Concave_4x0603
RN3: 10k; R_Array_Concave_4x0603
T1: FA2805; FA2924ALD
TP6, TP7, TP8, TP9, TP10, TP11, TP12, TP13, TP14, TP15, TP16, TP17, TP18, TP19, TP20: TestPoint; TestPoint_Pad_D1.5mm
U4: W5500; LQFP-48_7x7mm_P0.5mm
U5: VO618A-3X019T; SMDIP-4_W9.53mm_Clearance8mm
U6: SI3402-B-GMR; QFN-20_L5.0-W5.0-P0.80-TL-EP2.8; LCSC Part C510771
U7: TLV431; TSOT-23
Y2: ABM8-25.000MHZ-10-D1G-T; Crystal_SMD_3225-4Pin_3.2x2.5mm

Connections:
+3V3: C24.1, C25.1, C26.1, C27.1, C28.1, C29.1, C30.1, C31.1, C32.1, C60.1, L3.2 (TCT), L3.7 (RCT), R9.1, RN3.5 (R4.2), RN3.6 (R3.2), RN3.7 (R2.2), RN3.8 (R1.2), U4.4 (AVDD), U4.8 (AVDD), U4.11 (AVDD), U4.15 (AVDD), U4.17 (AVDD), U4.21 (AVDD), U4.28 (VDD); also elsewhere on the board
+LDO: C66.1, C67.1, LED1.2 (VDD), LED2.2 (VDD); also elsewhere on the board
/Ethernet/ACTLED: TP17.1 (1_1), U4.27 (ACTLED); also elsewhere on the board
/Ethernet/CT1: C33.1, C34.2, C43.1, D2.2 (A), D6.1 (K), L3.10 (RXCT), TP9.1 (1_1), U6.14 (CT1)
/Ethernet/CT2: C23.1, C35.2, C44.1, D3.2 (A), D7.1 (K), L3.15 (TXCT), TP8.1 (1_1), U6.13 (CT2)
/Ethernet/INTERRUPT: TP15.1 (1_1), U4.36 (~INT); also elsewhere on the board
/Ethernet/LINKLED: TP16.1 (1_1), U4.25 (LINKLED); also elsewhere on the board
/Ethernet/MISO: TP13.1 (1_1), U4.34 (MISO); also elsewhere on the board
/Ethernet/MOSI: TP14.1 (1_1), U4.35 (MOSI); also elsewhere on the board
/Ethernet/RD+: C40.2, L3.1 (TD+), RN2.1 (R1.1)
/Ethernet/RD-: C42.2, L3.3 (TD-), RN2.2 (R2.1)
/Ethernet/RST: C38.1, R9.2, TP10.1 (1_1), U4.37 (~RST); also elsewhere on the board
/Ethernet/RX+: J3.3, L3.16 (TX+)
/Ethernet/RX-: J3.6, L3.14 (TX-)
/Ethernet/RXN: R13.1, U4.5 (RXN)
/Ethernet/RXP: R12.1, U4.6 (RXP)
/Ethernet/SCK: TP12.1 (1_1), U4.33 (SCLK); also elsewhere on the board
/Ethernet/SCS: TP11.1 (1_1), U4.32 (~SCS); also elsewhere on the board
/Ethernet/SP1: C21.1, C36.2, C45.1, D4.2 (A), D8.1 (K), J3.7, J3.8, TP7.1 (1_1), U6.11 (SP1)
/Ethernet/SP2: C20.1, C37.2, C46.1, D5.2 (A), D9.1 (K), J3.4, J3.5, TP6.1 (1_1), U6.10 (SP2)
/Ethernet/TD+: L3.6 (RD+), R10.2, RN2.3 (R3.1)
/Ethernet/TD-: L3.8 (RD-), R11.2, RN2.4 (R4.1)
/Ethernet/TX+: J3.1, L3.11 (RX+)
/Ethernet/TX-: J3.2, L3.9 (RX-)
/Ethernet/TXN: R11.1, U4.1 (TXN)
/Ethernet/TXP: R10.1, U4.2 (TXP)
/Ethernet/V+: C34.1, C35.1, C36.1, C37.1, C47.2, C50.1, C51.1, C52.1, C53.1, C64.1, D2.1 (K), D3.1 (K), D4.1 (K), D5.1 (K), D11.1 (K), R24.2, T1.1, TP18.1 (1_1), U6.12 (VPOSF), U6.20 (FB)
/Ethernet/V-: C43.2, C44.2, C45.2, C46.2, C63.1, C64.2, D6.2 (A), D7.2 (A), D8.2 (A), D9.2 (A), R25.2, TP20.1 (1_1), U6.9 (VNEG), U6.21 (EP)
/LEDS_THRU: LED1.1 (DIN); also elsewhere on the board
GND: C22.2, C24.2, C25.2, C26.2, C27.2, C28.2, C29.2, C30.2, C31.2, C32.2, C38.2, C39.2, C41.2, C48.2, C49.2, C55.2, C56.2, C57.2, C58.2, C60.2, C63.2, C65.2, C66.2, C67.2, LED1.4 (GND), LED2.4 (GND), R17.2, R23.2, T1.9, T1.10, U4.3 (AGND), U4.9 (AGND), U4.14 (AGND), U4.16 (AGND), U4.19 (AGND), U4.29 (GND), U4.48 (AGND), U7.3 (A), Y2.2 (G), Y2.4 (G); also elsewhere on the board
GND1: C50.2, C51.2, C52.2, C53.2, C61.2, C62.2, U5.3, U6.7 (HSO), U6.19 (VSS2)
unnamed: C40.1, R12.2
unnamed: C42.1, R13.2
unnamed: C49.1, R14.1, R15.1, Y2.3
unnamed: C54.2, R16.1
unnamed: C59.2, R21.1
unnamed: C62.1, R20.2
unnamed: C65.1, J3.G1
unnamed: C54.1, D10.2 (A), T1.7, T1.8, TP19.1 (1_1)
unnamed: C56.1, D10.1 (K), L2.1, R16.2
unnamed: D11.2 (A), D12.2 (A)
unnamed: D12.1 (K), T1.2, U6.18 (SWO)
unnamed: LED1.3 (DO), LED2.1 (DIN)
unnamed: R19.1, U5.1
unnamed: C33.2, RN1.1 (R1.1)
unnamed: C22.1, RN1.5 (R4.2), RN1.6 (R3.2), RN1.7 (R2.2), RN1.8 (R1.2)
unnamed: C23.2, RN1.2 (R2.1)
unnamed: C21.2, RN1.3 (R3.1)
unnamed: C20.2, RN1.4 (R4.1)
unnamed: C41.1, RN2.7 (R2.2), RN2.8 (R1.2)
unnamed: C39.1, RN2.5 (R4.2), RN2.6 (R3.2)
unnamed: RN3.1 (R1.1), U4.45 (PMODE0)
unnamed: RN3.2 (R2.1), U4.44 (PMODE1)
unnamed: RN3.3 (R3.1), U4.43 (PMODE2)
unnamed: C57.1, U4.22 (1V2O)
unnamed: R17.1, U4.10 (EXRES1)
unnamed: C58.1, U4.20 (TOCAP)
unnamed: C48.1, R14.2, U4.30 (XI/CLKIN), Y2.1
unnamed: R15.2, U4.31 (XO)
unnamed: R18.2, R20.1, U5.4, U6.1 (EROUT)
unnamed: R25.1, U6.8 (RCL)
unnamed: R24.1, U6.6 (RDET)
unnamed: C59.1, U5.2, U7.2 (K)
unnamed: R21.2, R22.2, R23.1, U7.1 (Test)
VDD: C47.1, C55.1, C61.1, L2.2, R18.1, R19.2, R22.1, U6.3 (VDD); also elsewhere on the board

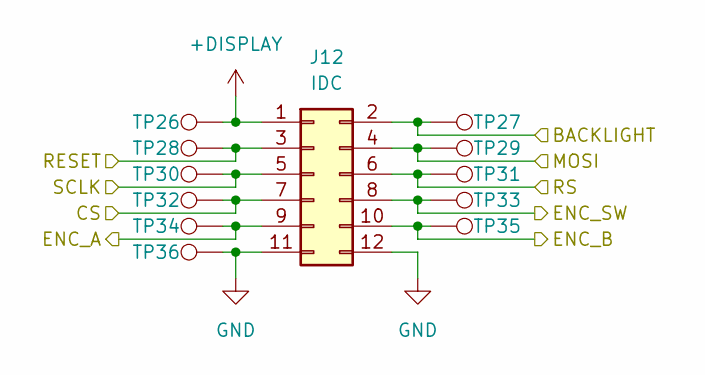
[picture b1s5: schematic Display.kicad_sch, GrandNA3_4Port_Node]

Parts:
J12: IDC; IDC-Header_2x06_P2.54mm_Vertical
TP26, TP27, TP28, TP29, TP30, TP31, TP32, TP33, TP34, TP35, TP36: TestPoint; TestPoint_Pad_D1.5mm

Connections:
+DISPLAY: J12.1, TP26.1 (1_1); also elsewhere on the board
/Display/BACKLIGHT: J12.2, TP27.1 (1_1); also elsewhere on the board
/Display/CS: J12.7, TP32.1 (1_1); also elsewhere on the board
/Display/ENC_A: J12.9, TP34.1 (1_1); also elsewhere on the board
/Display/ENC_B: J12.10, TP35.1 (1_1); also elsewhere on the board
/Display/ENC_SW: J12.8, TP33.1 (1_1); also elsewhere on the board
/Display/MOSI: J12.4, TP29.1 (1_1); also elsewhere on the board
/Display/RESET: J12.3, TP28.1 (1_1); also elsewhere on the board
/Display/RS: J12.6, TP31.1 (1_1); also elsewhere on the board
/Display/SCLK: J12.5, TP30.1 (1_1); also elsewhere on the board
GND: J12.11, J12.12, TP36.1 (1_1); also elsewhere on the board
